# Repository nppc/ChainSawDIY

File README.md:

# ChainSawDIY
DIY Battery ChainSaw for garden

AtMega8L fuses:

L=A4

H=D9

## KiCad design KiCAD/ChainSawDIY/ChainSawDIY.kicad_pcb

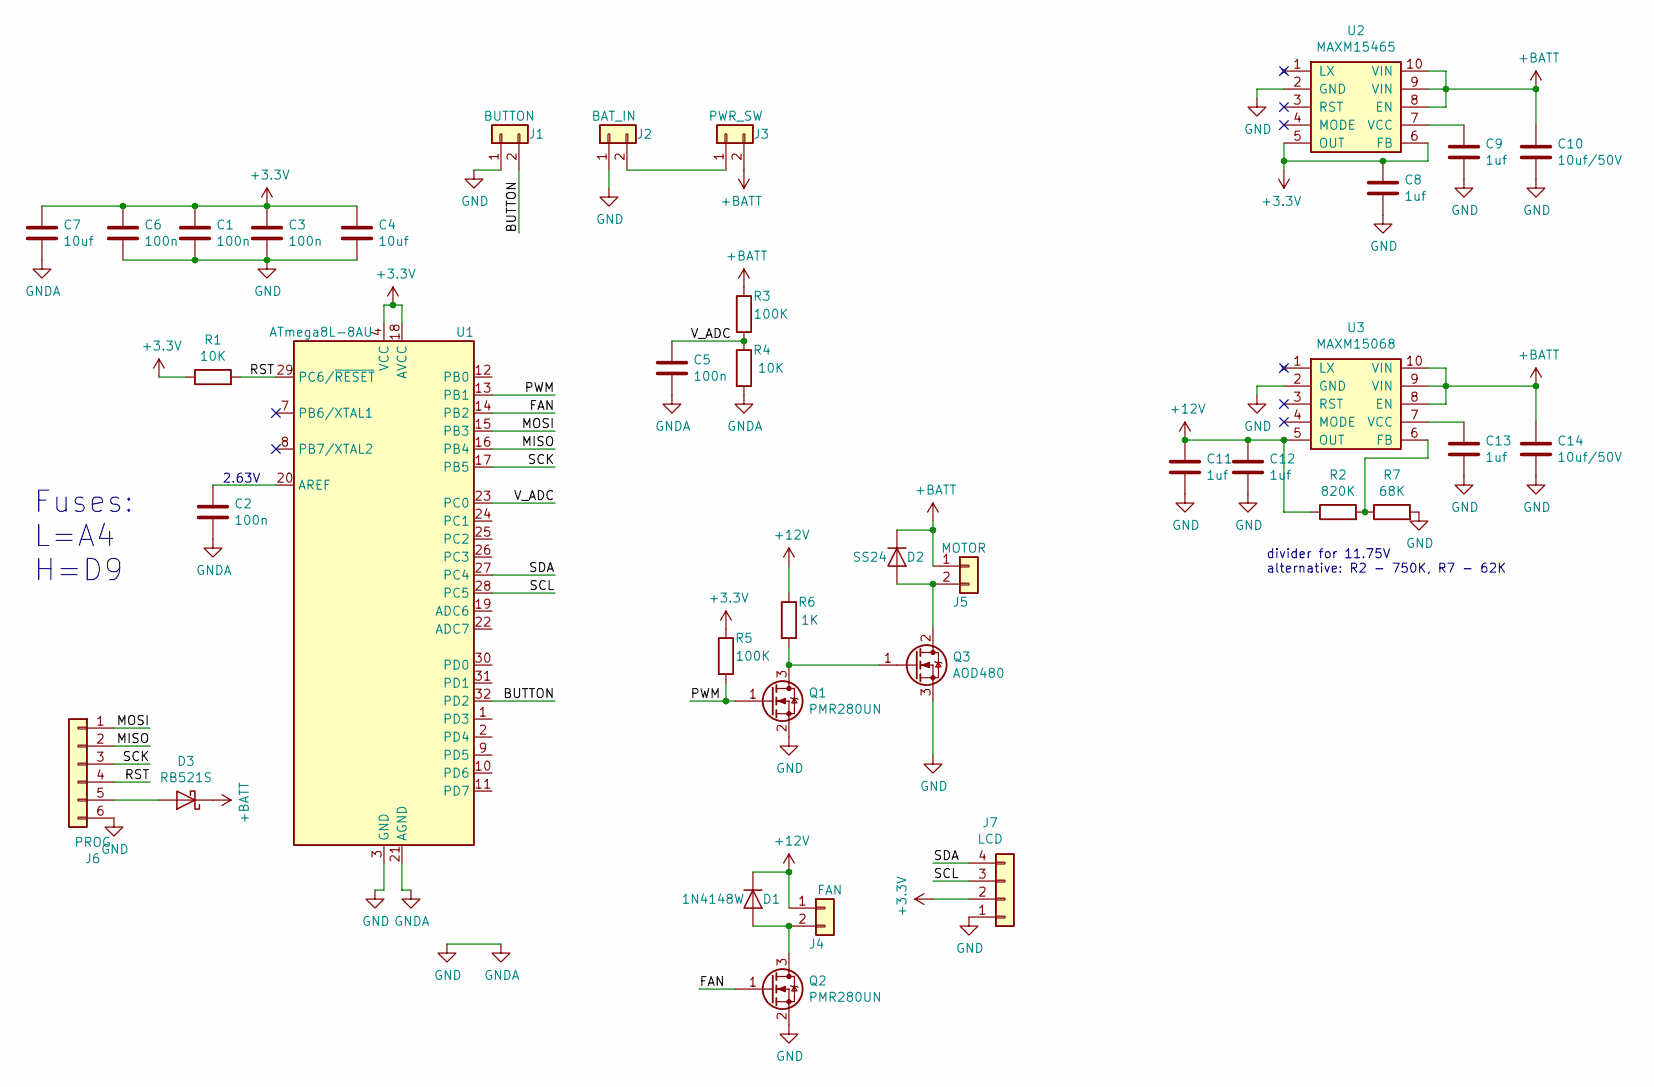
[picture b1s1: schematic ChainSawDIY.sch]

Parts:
C1, C2, C3, C5, C6: 100n; C_0603
C4, C7: 10uf; C_0603
C8, C9, C11, C12, C13: 1uf; C_0603
C10, C14: 10uf/50V; C_0603
D1: 1N4148W; D_SOD-123
D2: SS24; D_SMB
D3: RB521S; D_SOD-523
J1: BUTTON; Conn2pin_2.54mm
J2: BAT_IN; Conn_Power
J3: PWR_SW; Conn_Power
J4: FAN; Conn2pin_2.54mm
J5: MOTOR; Conn_Power
J6: PROG; Molex_PicoBlade_53047-0610_06x1.25mm_Straight
J7: LCD; Pin_Header_Straight_1x04_Pitch2.54mm
Q1, Q2: PMR280UN; SC75-3
Q3: AOD480; TO-252-2_Rectifier
R1, R4: 10K; R_0603
R2: 820K; R_0603
R3, R5: 100K; R_0603
R6: 1K; R_0603
R7: 68K; R_0603
U1: ATmega8L-8AU; LQFP-32_7x7mm_Pitch0.8mm
U2: MAXM15465
U3: MAXM15068; MAXM15465

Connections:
+3V3: C1.1, C3.1, C4.1, C6.1, C7.1, C8.1, J7.2, R1.1, R5.1, U1.4 (VCC), U1.6 (VCC), U1.18 (AVCC), U2.5 (OUT), U2.6 (FB)
+12V: C11.1, C12.1, D1.1 (K), J4.1, R2.1, R6.1, U3.5 (OUT)
+BATT: C10.1, C14.1, D2.1 (K), D3.1 (K), J3.2, J5.1, R3.1, U2.8 (EN), U2.9 (VIN), U2.10 (VIN), U3.8 (EN), U3.9 (VIN), U3.10 (VIN)
/BUTTON: J1.2, U1.32 (PD2)
/FAN: Q2.1 (G), U1.14 (PB2)
/MISO: J6.2, U1.16 (PB4)
/MOSI: J6.1, U1.15 (PB3)
/PWM: Q1.1 (G), R5.2, U1.13 (PB1)
/RST: J6.4, R1.2, U1.29 (PC6/~RESET)
/SCK: J6.3, U1.17 (PB5)
/SCL: J7.3, U1.28 (PC5)
/SDA: J7.4, U1.27 (PC4)
/V_ADC: C5.1, R3.2, R4.1, U1.23 (PC0)
GND: C1.2, C2.2, C3.2, C4.2, C5.2, C6.2, C7.2, C8.2, C9.2, C10.2, C11.2, C12.2, C13.2, C14.2, J1.1, J2.1, J6.6, J7.1, Q1.2 (S), Q2.2 (S), Q3.3 (S), R4.2, R7.2, U1.3 (GND), U1.5 (GND), U1.21 (AGND), U2.2 (GND), U3.2 (GND)
unnamed: C2.1, U1.20 (AREF)
unnamed: C9.1, U2.7 (VCC)
unnamed: C13.1, U3.7 (VCC)
unnamed: D1.2 (A), J4.2, Q2.3 (D)
unnamed: D2.2 (A), J5.2, Q3.2 (D)
unnamed: D3.2 (A), J6.5
unnamed: J2.2, J3.1
unnamed: Q1.3 (D), Q3.1 (G), R6.2
unnamed: R2.2, R7.1, U3.6 (FB)

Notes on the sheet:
divider for 11.75V alternative: R2 - 750K, R7 - 62K
2.63V
Fuses: L=A4 H=D9

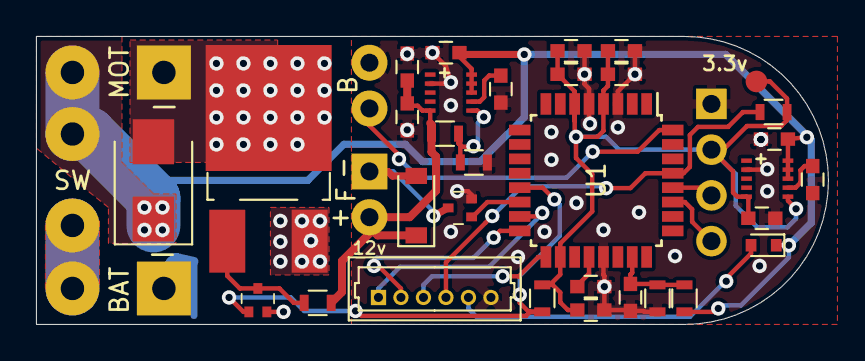
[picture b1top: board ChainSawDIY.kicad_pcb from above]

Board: 2 copper layers, 44.0 x 16.0 mm, 37 parts (1 on the bottom side), 23 nets.

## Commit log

2019-09-02 Initial commit of SCAD
2019-09-02 Scad wooden holder
2019-09-03 Prepare dxf files for milling
2019-09-03 CNC preparations
2019-09-06 some updates to scad
2019-09-07 CNC finished
2019-09-08 Firmware
2019-09-09 trying another oled library
2019-09-09 new oled firmware working
2019-09-09 added most of the functionality to firmware
2019-09-09 bugs fixed
2019-09-10 enclosure
2019-09-10 Electronics enclosure scad
2019-09-10 Handle project
2019-09-11 add switch project
2019-09-11 Handle reworked
2019-09-11 Switch made smaller
2019-09-11 Switch check
2019-09-12 fixed internal perimeter of enclosure
2019-09-12 pushswitch ready to print
2019-09-12 smooth start
2019-09-12 firmware alfa version is ready
2019-09-13 switch rework
2019-09-14 firmware beta version ready to test
2019-09-15 some final cnc
2019-09-16 make switch case thinner
2019-09-17 make even better fit of switch
2019-09-17 Add watchdog to firmware
2019-09-18 stop if battery low while starting
2019-09-18 Add watchdog to firmware and fix startmotor function def
2019-10-18 motor cover
2019-10-21 BatteryHolder
2020-08-06 mega8 C firmware
2020-08-07 add gitignore
2020-08-07 alfa version ready
2020-08-07 bit manipulations
2020-08-07 beta version is ready
2020-08-07 slight schematic adjustments
2020-08-07 Openscad models
2020-08-13 selectable oled compilation
2020-10-03 Fuse data
2020-10-03 PCB Image
2020-10-03 Add pcb Image
